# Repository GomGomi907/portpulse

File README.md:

# PortPulse

## 무엇인가

PortPulse는 PC와 USB 장치(DUT) 사이에 연결하는 USB 2.0 재연결 동글입니다.

PC와 제어 MCU의 연결은 유지한 채, 외부 DUT의 VBUS와 D+/D−를 소프트웨어로
차단하고 복구합니다. 따라서 USB 장치를 실제로 뽑았다가 다시 연결하는 동작을
자동화 테스트에서 재현할 수 있습니다.

## 사용 방법

1. PortPulse의 USB-C upstream 포트를 PC에 연결합니다.
2. DUT를 PortPulse의 USB-A downstream 포트에 연결합니다.
3. 장치 관리자에서 PortPulse의 COM 포트 번호를 확인합니다.
4. 네이티브 `portpulse` 프로그램으로 명령을 보냅니다.

```text
portpulse --port COM12 status
portpulse --port COM12 on
portpulse --port COM12 off
portpulse --port COM12 --delay-ms 2000 cycle
```

주요 명령:

- `on`: DUT 연결
- `off`: DUT 차단
- `cycle`: DUT를 차단한 뒤 지정한 시간 후 다시 연결
- `status`: 현재 상태 확인
- `fault`: 전원 스위치 Fault 상태 확인
- `version`: 펌웨어 버전 확인

현재 Rev.C.1은 DUT 1포트를 지원합니다. 여러 PortPulse를 연결하는 경우에는
각 장치의 COM 포트를 지정해서 사용합니다.

하드웨어·펌웨어·호스트 프로그램은 MIT License로 배포합니다. 제3자 구성요소는
각 구성요소의 고지 파일을 따릅니다.

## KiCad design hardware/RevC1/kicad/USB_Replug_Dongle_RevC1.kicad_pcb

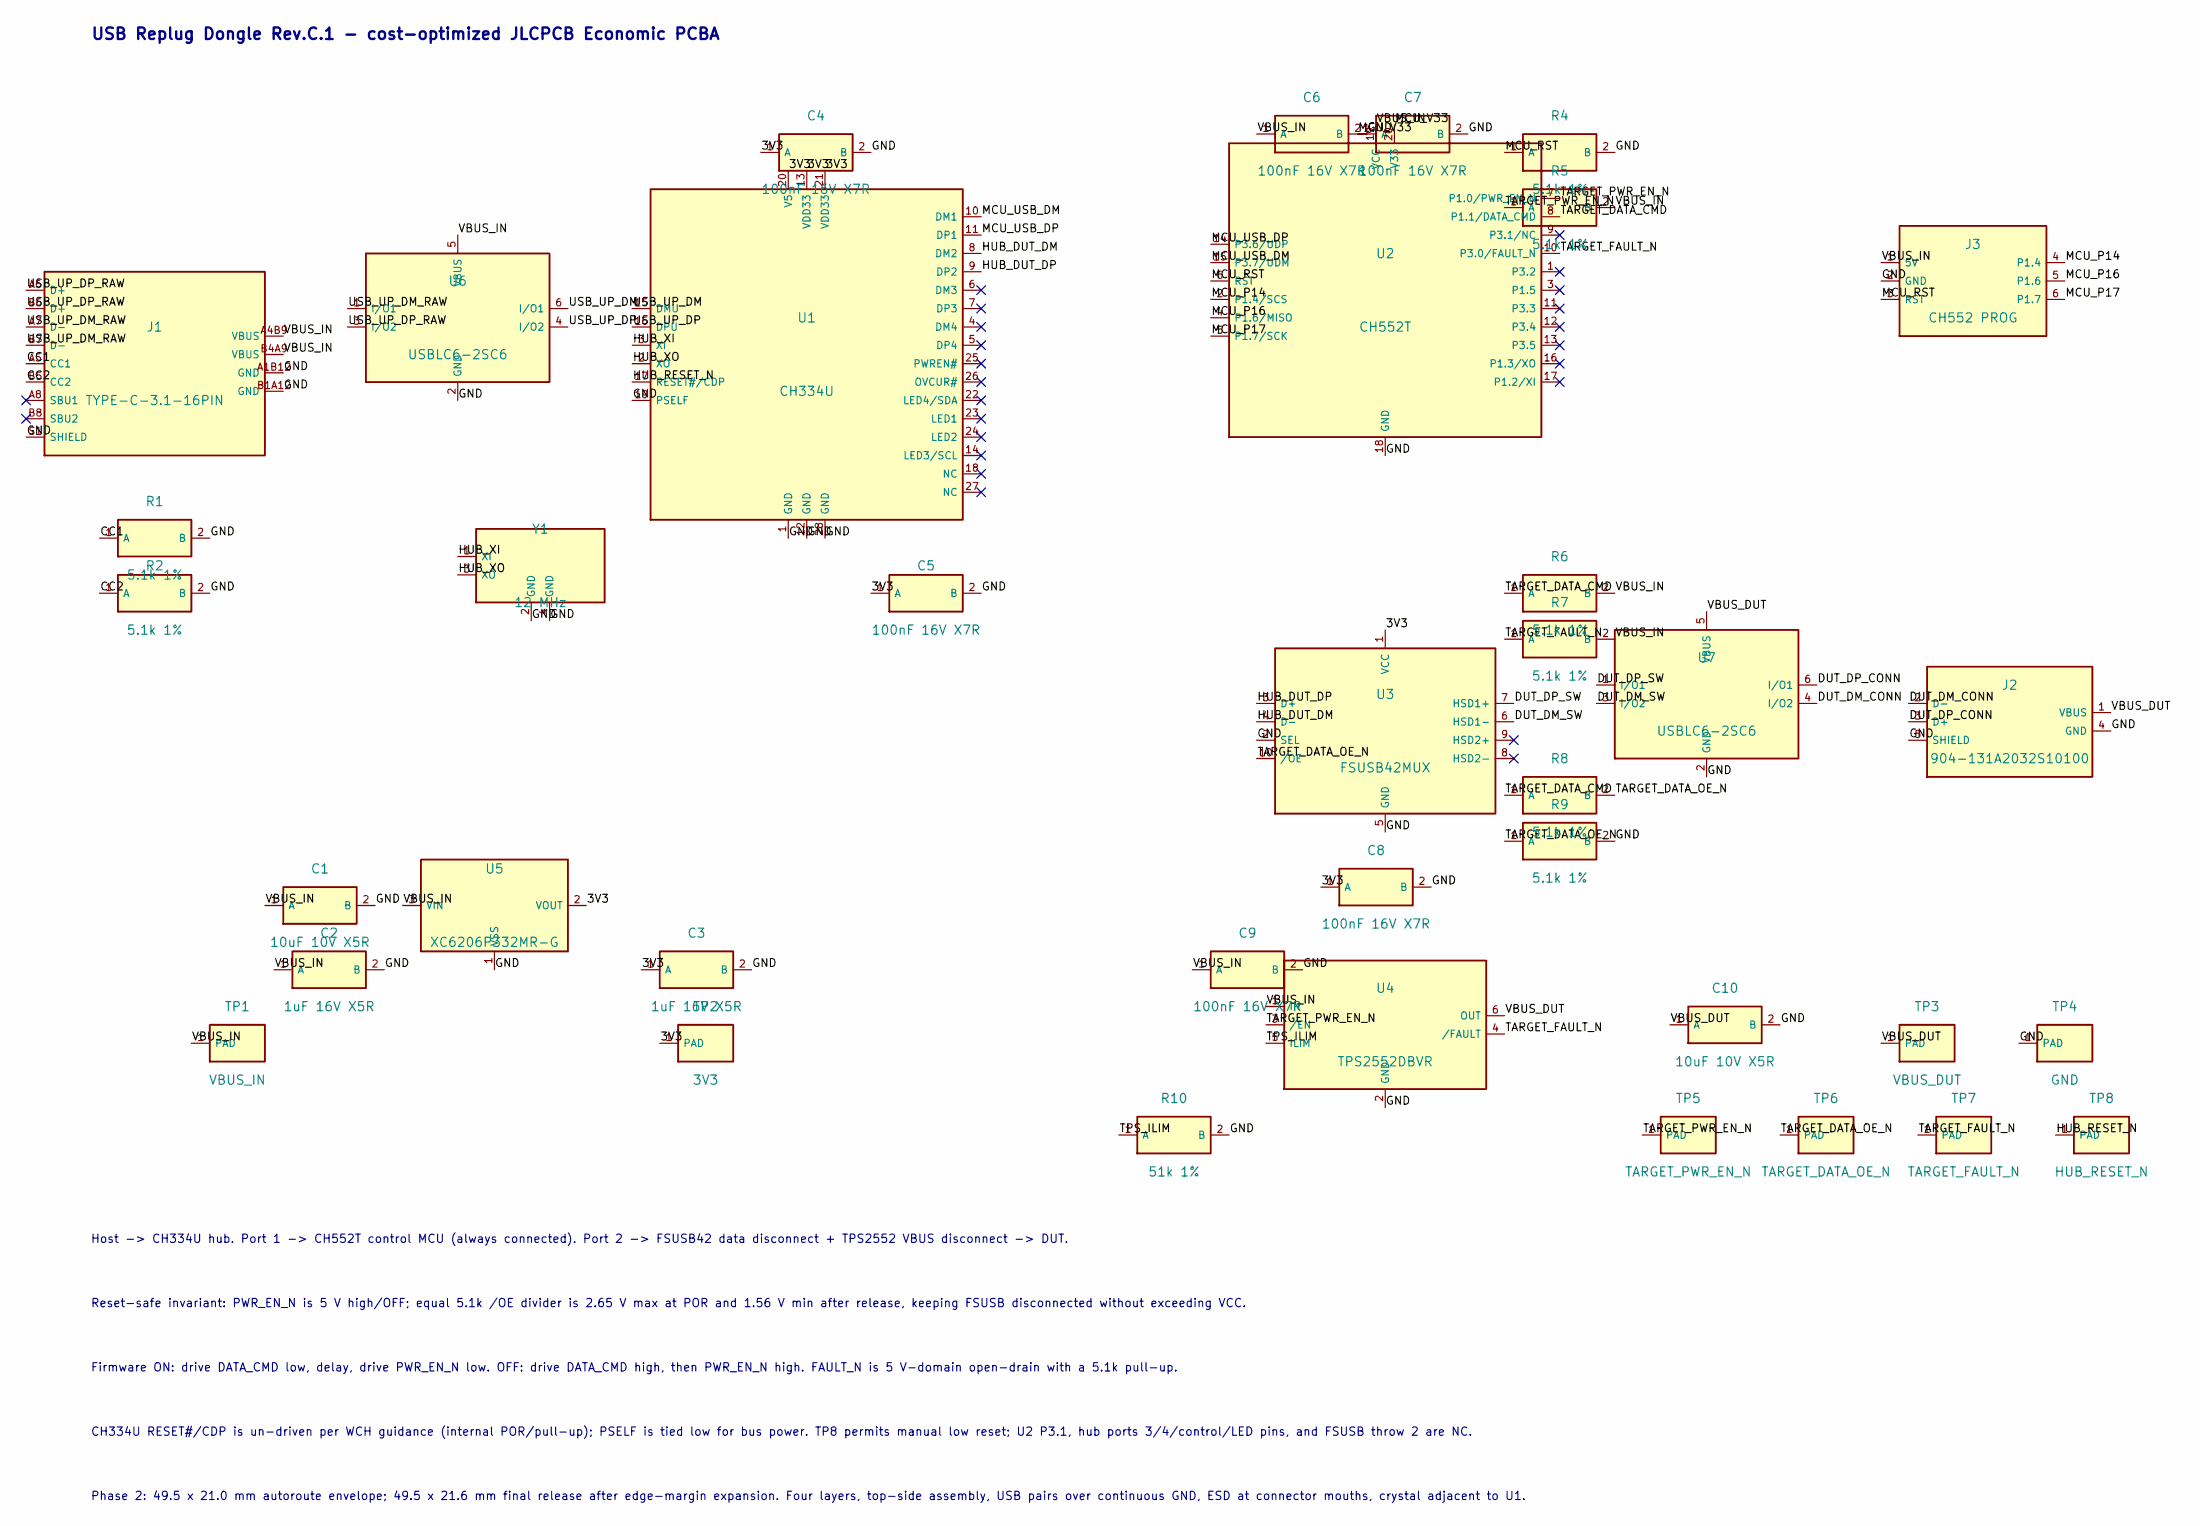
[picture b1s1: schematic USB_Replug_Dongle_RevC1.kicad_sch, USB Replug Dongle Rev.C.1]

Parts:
C1, C10: 10uF 10V X5R; C_0603_1608Metric; MPN 10uF 10V X5R; LCSC Part # C19702
C2, C3: 1uF 16V X5R; C_0603_1608Metric; MPN 1uF 16V X5R; LCSC Part # C15849
C4, C5, C6, C7, C8, C9: 100nF 16V X7R; C_0603_1608Metric; MPN 100nF 16V X7R; LCSC Part # C14663
J1: TYPE-C-3.1-16PIN; C7507405_USB_C; MPN TYPE-C-3.1-16PIN; LCSC Part # C7507405
J2: 904-131A2032S10100; C8328_USB_A; MPN 904-131A2032S10100; LCSC Part # C8328
J3: CH552 PROG; PROG_PADS_2x3_P1.27
R1, R2, R4, R5, R6, R7, R8, R9: 5.1k 1%; R_0603_1608Metric; MPN 5.1k 1%; LCSC Part # C23186
R10: 51k 1%; R_0603_1608Metric; MPN 51k 1%; LCSC Part # C107231
TP1: VBUS_IN; TP_Pad_0.7mm
TP2: 3V3; TP_Pad_0.7mm
TP3: VBUS_DUT; TP_Pad_0.7mm
TP4: GND; TP_Pad_0.7mm
TP5: TARGET_PWR_EN_N; TP_Pad_0.7mm
TP6: TARGET_DATA_OE_N; TP_Pad_0.7mm
TP7: TARGET_FAULT_N; TP_Pad_0.7mm
TP8: HUB_RESET_N; TP_Pad_0.7mm
U1: CH334U; QSOP-28_3.9x9.9mm_P0.635mm; MPN CH334U; LCSC Part # C5187524
U2: CH552T; TSSOP-20_4.4x6.5mm_P0.65mm; MPN CH552T; LCSC Part # C111367
U3: FSUSB42MUX; MSOP-10_3x3mm_P0.5mm; MPN FSUSB42MUX; LCSC Part # C11355
U4: TPS2552DBVR; SOT-23-6; MPN TPS2552DBVR; LCSC Part # C46506
U5: XC6206P332MR-G; SOT-23; MPN XC6206P332MR-G; LCSC Part # C5446
U6, U7: USBLC6-2SC6; SOT-23-6; MPN USBLC6-2SC6; LCSC Part # C7519
Y1: 12 MHz; Crystal_SMD_3225-4Pin_3.2x2.5mm; MPN X322512MSB4SI; LCSC Part # C9002

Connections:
/3V3: C3.1 (A), C4.1 (A), C5.1 (A), C8.1 (A), TP2.1, U1.13 (VDD33), U1.20 (V5), U1.21 (VDD33), U3.1 (VCC), U5.2 (VOUT)
/CC1: J1.A5 (CC1), R1.1 (A)
/CC2: J1.B5 (CC2), R2.1 (A)
/DUT_DM_CONN: J2.2 (D-), U7.4 (I/O2)
/DUT_DM_SW: U3.6 (HSD1-), U7.3 (I/O2)
/DUT_DP_CONN: J2.3 (D+), U7.6 (I/O1)
/DUT_DP_SW: U3.7 (HSD1+), U7.1 (I/O1)
/GND: C1.2 (B), C2.2 (B), C3.2 (B), C4.2 (B), C5.2 (B), C6.2 (B), C7.2 (B), C8.2 (B), C9.2 (B), C10.2 (B), J1.A1B12 (GND), J1.B1A12 (GND), J1.S1 (SHIELD), J2.4 (GND), J2.5 (SHIELD), J3.2 (GND), R1.2 (B), R2.2 (B), R4.2 (B), R9.2 (B), R10.2 (B), TP4.1, U1.1 (GND), U1.12 (GND), U1.19 (PSELF), U1.28 (GND), U2.18 (GND), U3.2 (SEL), U3.5 (GND), U4.2 (GND), U5.1 (VSS), U6.2 (GND), U7.2 (GND), Y1.2 (GND), Y1.4 (GND)
/HUB_DUT_DM: U1.8 (DM2), U3.4 (D-)
/HUB_DUT_DP: U1.9 (DP2), U3.3 (D+)
/HUB_RESET_N: TP8.1, U1.17 (RESET#/CDP)
/HUB_XI: U1.3 (XI), Y1.1 (XI)
/HUB_XO: U1.2 (XO), Y1.3 (XO)
/MCU_P14: J3.4 (P1.4), U2.2 (P1.4/SCS)
/MCU_P16: J3.5 (P1.6), U2.4 (P1.6/MISO)
/MCU_P17: J3.6 (P1.7), U2.5 (P1.7/SCK)
/MCU_RST: J3.3 (RST), R4.1 (A), U2.6 (RST)
/MCU_USB_DM: U1.10 (DM1), U2.15 (P3.7/UDM)
/MCU_USB_DP: U1.11 (DP1), U2.14 (P3.6/UDP)
/MCU_V33: C7.1 (A), U2.20 (V33)
/TARGET_DATA_CMD: R6.1 (A), R8.1 (A), U2.8 (P1.1/DATA_CMD)
/TARGET_DATA_OE_N: R8.2 (B), R9.1 (A), TP6.1, U3.10 (/OE)
/TARGET_FAULT_N: R7.1 (A), TP7.1, U2.10 (P3.0/FAULT_N), U4.4 (/FAULT)
/TARGET_PWR_EN_N: R5.1 (A), TP5.1, U2.7 (P1.0/PWR_EN_N), U4.3 (/EN)
/TPS_ILIM: R10.1 (A), U4.5 (ILIM)
/USB_UP_DM: U1.15 (DMU), U6.6 (I/O1)
/USB_UP_DM_RAW: J1.A7 (D-), J1.B7 (D-), U6.1 (I/O1)
/USB_UP_DP: U1.16 (DPU), U6.4 (I/O2)
/USB_UP_DP_RAW: J1.A6 (D+), J1.B6 (D+), U6.3 (I/O2)
/VBUS_DUT: C10.1 (A), J2.1 (VBUS), TP3.1, U4.6 (OUT), U7.5 (VBUS)
/VBUS_IN: C1.1 (A), C2.1 (A), C6.1 (A), C9.1 (A), J1.A4B9 (VBUS), J1.B4A9 (VBUS), J3.1 (5V), R5.2 (B), R6.2 (B), R7.2 (B), TP1.1, U2.19 (VCC), U4.1 (IN), U5.3 (VIN), U6.5 (VBUS)

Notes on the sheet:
USB Replug Dongle Rev.C.1 - cost-optimized JLCPCB Economic PCBA
Host -> CH334U hub. Port 1 -> CH552T control MCU (always connected). Port 2 -> FSUSB42 data disconnect + TPS2552 VBUS disconnect -> DUT.
Reset-safe invariant: PWR_EN_N is 5 V high/OFF; equal 5.1k /OE divider is 2.65 V max at POR and 1.56 V min after release, keeping FSUSB disconnected without exceeding VCC.
Firmware ON: drive DATA_CMD low, delay, drive PWR_EN_N low. OFF: drive DATA_CMD high, then PWR_EN_N high. FAULT_N is 5 V-domain open-drain with a 5.1k pull-up.
CH334U RESET#/CDP is un-driven per WCH guidance (internal POR/pull-up); PSELF is tied low for bus power. TP8 permits manual low reset; U2 P3.1, hub ports 3/4/control/LED pins, and FSUSB throw 2 are NC.
Phase 2: 49.5 x 21.0 mm autoroute envelope; 49.5 x 21.6 mm final release after edge-margin expansion. Four layers, top-side assembly, USB pairs over continuous GND, ESD at connector mouths, crystal adjacent to U1.

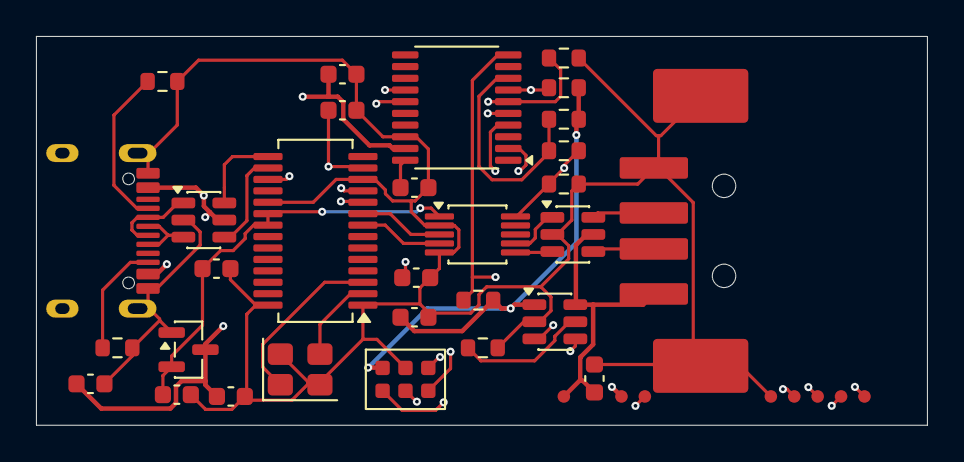
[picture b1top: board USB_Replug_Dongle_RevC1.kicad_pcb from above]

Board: 4 copper layers, 49.5 x 21.6 mm, 38 parts (0 on the bottom side), 31 nets.

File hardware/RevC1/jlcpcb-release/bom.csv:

Designator,Footprint,Quantity,Value,LCSC Part #,MPN,Manufacturer,Assembly Notes
"C1,C10",Capacitor_SMD:C_0603_1608Metric,2,10uF 10V X5R,C19702,10uF 10V X5R,Generic,Top SMT; JLCPCB Economic PCBA
"C2,C3",Capacitor_SMD:C_0603_1608Metric,2,1uF 16V X5R,C15849,1uF 16V X5R,Generic,Top SMT; JLCPCB Economic PCBA
"C4,C5,C6,C7,C8,C9",Capacitor_SMD:C_0603_1608Metric,6,100nF 16V X7R,C14663,100nF 16V X7R,Generic,Top SMT; JLCPCB Economic PCBA
J1,USB_Replug_Dongle_RevC1:C7507405_USB_C,1,TYPE-C-3.1-16PIN,C7507405,TYPE-C-3.1-16PIN,SHOU HAN,Top SMT/PTH shell; opening at left edge
J2,USB_Replug_Dongle_RevC1:C8328_USB_A,1,904-131A2032S10100,C8328,904-131A2032S10100,Jing Extension of the Electronic Co.,Top SMT/PTH locating holes; opening at right edge
"R1,R2,R4,R5,R6,R7,R8,R9",Resistor_SMD:R_0603_1608Metric,8,5.1k 1%,C23186,5.1k 1%,Generic,Top SMT; JLCPCB Economic PCBA
R10,Resistor_SMD:R_0603_1608Metric,1,51k 1%,C107231,51k 1%,Generic,Top SMT; JLCPCB Economic PCBA
U1,Package_SO:QSOP-28_3.9x9.9mm_P0.635mm,1,CH334U,C5187524,CH334U,WCH,Top SMT; JLCPCB Economic PCBA
U2,Package_SO:TSSOP-20_4.4x6.5mm_P0.65mm,1,CH552T,C111367,CH552T,WCH,Top SMT; JLCPCB Economic PCBA
U3,Package_SO:MSOP-10_3x3mm_P0.5mm,1,FSUSB42MUX,C11355,FSUSB42MUX,onsemi,Top SMT; JLCPCB Economic PCBA
U4,Package_TO_SOT_SMD:SOT-23-6,1,TPS2552DBVR,C46506,TPS2552DBVR,Texas Instruments,Top SMT; JLCPCB Economic PCBA
U5,Package_TO_SOT_SMD:SOT-23,1,XC6206P332MR-G,C5446,XC6206P332MR-G,Torex,Top SMT; JLCPCB Economic PCBA
"U6,U7",Package_TO_SOT_SMD:SOT-23-6,2,USBLC6-2SC6,C7519,USBLC6-2SC6,STMicroelectronics,Top SMT; JLCPCB Economic PCBA
Y1,Crystal:Crystal_SMD_3225-4Pin_3.2x2.5mm,1,12 MHz,C9002,X322512MSB4SI,YXC,Top SMT; JLCPCB Economic PCBA
